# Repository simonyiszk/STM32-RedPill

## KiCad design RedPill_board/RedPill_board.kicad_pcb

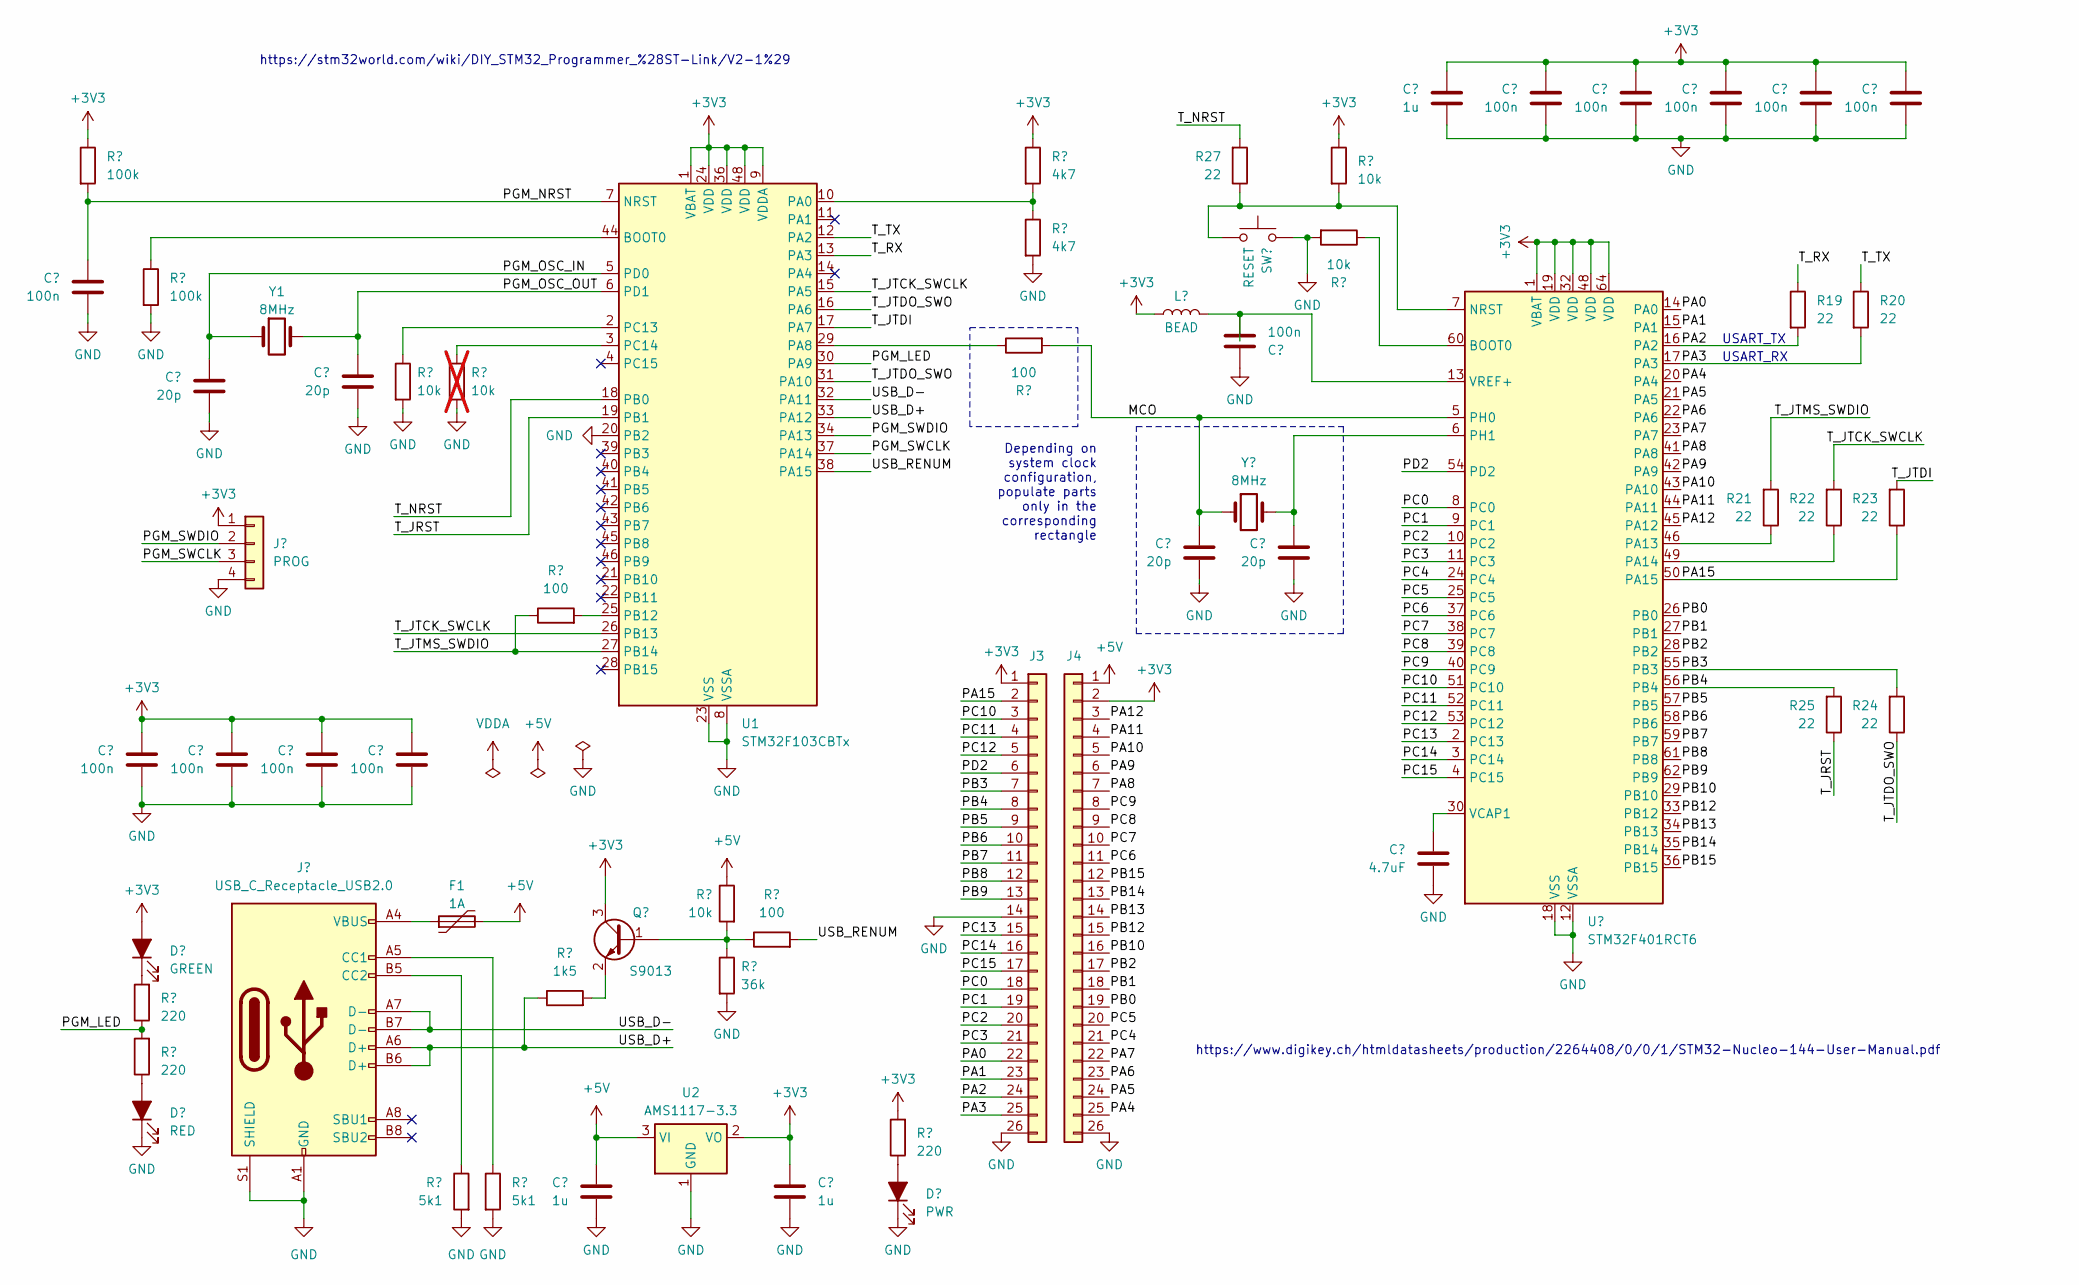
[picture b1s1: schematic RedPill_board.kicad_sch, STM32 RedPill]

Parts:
C1, C2, C3, C5, C7, C12, C15, C16, C17, C18, C19: 100n; C_0603_1608Metric
C4, C6, C10, C11: 20p; C_0603_1608Metric
C8, C9, C14: 1u; C_0603_1608Metric
C13: 4.7uF; C_0805_2012Metric
D1: GREEN; LED_0603_1608Metric
D2: RED; LED_0603_1608Metric
D3: PWR; LED_0603_1608Metric
F1: 1A; Fuse_1206_3216Metric
J1: PROG; PinHeader_1x04_P1.27mm_Vertical
J2: USB_C_Receptacle_USB2.0; USB_C_Receptacle_G-Switch_GT-USB-7010ASV
J3, J4: Conn_01x26; PinHeader_1x26_P2.54mm_Vertical
L1: BEAD; L_0603_1608Metric
Q1: S9013; SOT-23
R1, R4: 100k; R_0603_1608Metric
R2, R3, R15: 220; R_0603_1608Metric
R5, R11, R18, R26: 10k; R_0603_1608Metric
R6: 10k; R_0603_1608Metric; not fitted
R7, R8: 5k1; R_0603_1608Metric
R9, R13, R14: 100; R_0603_1608Metric
R10: 1k5; R_0603_1608Metric
R12: 36k; R_0603_1608Metric
R16, R17: 4k7; R_0603_1608Metric
R19, R20, R21, R22, R23, R24, R25, R27: 22; R_0603_1608Metric
SW1: RESET; SW_SPST_TL3342
U1: STM32F103CBTx; LQFP-48_7x7mm_P0.5mm
U2: AMS1117-3.3; SOT-223-3_TabPin2
U3: STM32F401RCT6; LQFP-64_10x10mm_P0.5mm
Y1: 8MHz; Crystal_SMD_5032-2Pin_5.0x3.2mm
Y2: 8MHz; Crystal_HC49-4H_Vertical

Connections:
+3V3: C2.1, C3.1, C5.1, C7.1, C9.1, C14.1, C15.1, C16.1, C17.1, C18.1, C19.1, D1.2 (A), J1.1, J3.1, J4.2, L1.1, Q1.3 (C), R1.1, R15.2, R16.1, R26.1, U1.1 (VBAT), U1.9 (VDDA), U1.24 (VDD), U1.36 (VDD), U1.48 (VDD), U2.2 (VO), U3.1 (VBAT), U3.19 (VDD), U3.32 (VDD), U3.48 (VDD), U3.64 (VDD)
+5V: C8.1, F1.2, J4.1, R11.1, U2.3 (VI)
/MCO: C10.1, R14.2, U3.5 (PH0), Y2.1
/PA0: J3.22, U3.14 (PA0)
/PA1: J3.23, U3.15 (PA1)
/PA2: J3.24, R19.2, U3.16 (PA2)
/PA3: J3.25, R20.2, U3.17 (PA3)
/PA4: J4.25, U3.20 (PA4)
/PA5: J4.24, U3.21 (PA5)
/PA6: J4.23, U3.22 (PA6)
/PA7: J4.22, U3.23 (PA7)
/PA8: J4.7, U3.41 (PA8)
/PA9: J4.6, U3.42 (PA9)
/PA10: J4.5, U3.43 (PA10)
/PA11: J4.4, U3.44 (PA11)
/PA12: J4.3, U3.45 (PA12)
/PA15: J3.2, R23.1, U3.50 (PA15)
/PB0: J4.19, U3.26 (PB0)
/PB1: J4.18, U3.27 (PB1)
/PB2: J4.17, U3.28 (PB2)
/PB3: J3.7, R24.2, U3.55 (PB3)
/PB4: J3.8, R25.2, U3.56 (PB4)
/PB5: J3.9, U3.57 (PB5)
/PB6: J3.10, U3.58 (PB6)
/PB7: J3.11, U3.59 (PB7)
/PB8: J3.12, U3.61 (PB8)
/PB9: J3.13, U3.62 (PB9)
/PB10: J4.16, U3.29 (PB10)
/PB12: J4.15, U3.33 (PB12)
/PB13: J4.14, U3.34 (PB13)
/PB14: J4.13, U3.35 (PB14)
/PB15: J4.12, U3.36 (PB15)
/PC0: J3.18, U3.8 (PC0)
/PC1: J3.19, U3.9 (PC1)
/PC2: J3.20, U3.10 (PC2)
/PC3: J3.21, U3.11 (PC3)
/PC4: J4.21, U3.24 (PC4)
/PC5: J4.20, U3.25 (PC5)
/PC6: J4.11, U3.37 (PC6)
/PC7: J4.10, U3.38 (PC7)
/PC8: J4.9, U3.39 (PC8)
/PC9: J4.8, U3.40 (PC9)
/PC10: J3.3, U3.51 (PC10)
/PC11: J3.4, U3.52 (PC11)
/PC12: J3.5, U3.53 (PC12)
/PC13: J3.15, U3.2 (PC13)
/PC14: J3.16, U3.3 (PC14)
/PC15: J3.17, U3.4 (PC15)
/PD2: J3.6, U3.54 (PD2)
/PGM_LED: R2.1, R3.2, U1.30 (PA9)
/PGM_NRST: C1.1, R1.2, U1.7 (NRST)
/PGM_OSC_IN: C4.1, U1.5 (PD0), Y1.1
/PGM_OSC_OUT: C6.1, U1.6 (PD1), Y1.2
/PGM_SWCLK: J1.3, U1.37 (PA14)
/PGM_SWDIO: J1.2, U1.34 (PA13)
/T_JRST: R25.1, U1.19 (PB1)
/T_JTCK_SWCLK: R22.2, U1.15 (PA5), U1.26 (PB13)
/T_JTDI: R23.2, U1.17 (PA7)
/T_JTDO_SWO: R24.1, U1.16 (PA6), U1.31 (PA10)
/T_JTMS_SWDIO: R9.1, R21.2, U1.27 (PB14)
/T_NRST: R27.2, U1.18 (PB0)
/T_RX: R19.1, U1.13 (PA3)
/T_TX: R20.1, U1.12 (PA2)
/USB_D+: J2.A6 (D+), J2.B6 (D+), R10.1, U1.33 (PA12)
/USB_D-: J2.A7 (D-), J2.B7 (D-), U1.32 (PA11)
/USB_RENUM: R13.2, U1.38 (PA15)
GND: C1.2, C2.2, C3.2, C4.2, C5.2, C6.2, C7.2, C8.2, C9.2, C10.2, C11.2, C12.1, C13.2, C14.2, C15.2, C16.2, C17.2, C18.2, C19.2, D2.1 (K), D3.1 (K), J1.4, J2.A1 (GND), J2.A12 (GND), J2.B1 (GND), J2.B12 (GND), J2.S1 (SHIELD), J3.14, J3.26, J4.26, R4.2, R5.2, R6.2, R7.2, R8.2, R12.2, R17.2, R18.2, SW1.2, U1.8 (VSSA), U1.20 (PB2), U1.23 (VSS), U1.35 (VSS), U1.47 (VSS), U2.1 (GND), U3.12 (VSSA), U3.18 (VSS), U3.31 (VSS), U3.47 (VSS), U3.63 (VSS)
unnamed: D1.1 (K), R2.2
unnamed: D2.2 (A), R3.1
unnamed: D3.2 (A), R15.1
unnamed: F1.1, J2.A4 (VBUS), J2.A9 (VBUS), J2.B4 (VBUS), J2.B9 (VBUS)
unnamed: J2.A5 (CC1), R8.1
unnamed: J2.B5 (CC2), R7.1
unnamed: Q1.1 (B), R11.2, R12.1, R13.1
unnamed: Q1.2 (E), R10.2
unnamed: R4.1, U1.44 (BOOT0)
unnamed: R16.2, R17.1, U1.10 (PA0)
unnamed: R14.1, U1.29 (PA8)
unnamed: R9.2, U1.25 (PB12)
unnamed: R5.1, U1.2 (PC13)
unnamed: R6.1, U1.3 (PC14)
unnamed: R18.1, U3.60 (BOOT0)
unnamed: R26.2, R27.1, SW1.1, U3.7 (NRST)
unnamed: R21.1, U3.46 (PA13)
unnamed: R22.1, U3.49 (PA14)
unnamed: C11.1, U3.6 (PH1), Y2.2
unnamed: C13.1, U3.30 (VCAP1)
unnamed: C12.2, L1.2, U3.13 (VREF+)

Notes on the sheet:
Depending on system clock configuration, populate parts only in the corresponding rectangle
https://stm32world.com/wiki/DIY_STM32_Programmer_%28ST-Link/V2-1%29
USART_RX
USART_TX
https://www.digikey.ch/htmldatasheets/production/2264408/0/0/1/STM32-Nucleo-144-User-Manual.pdf

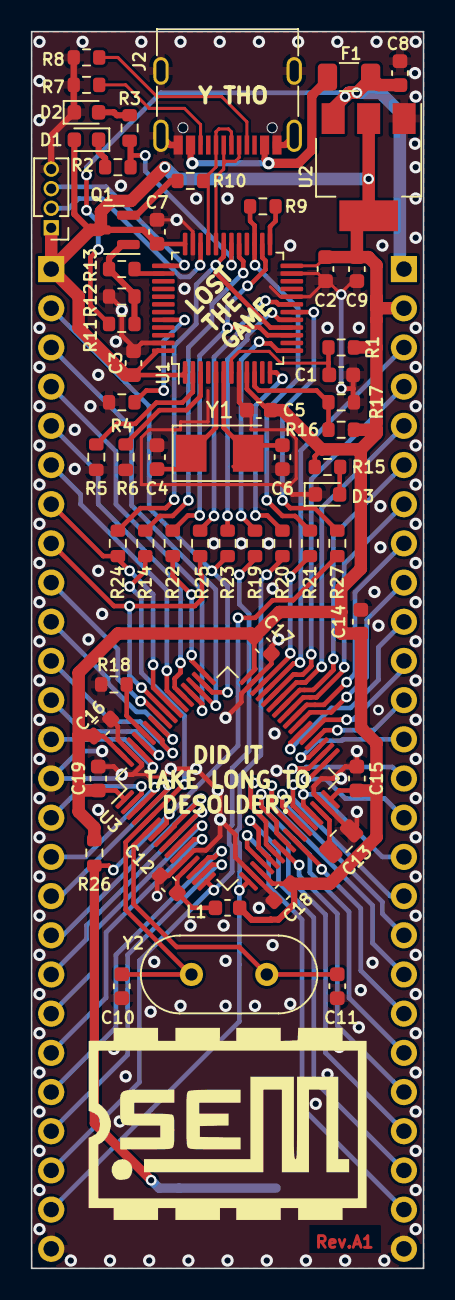
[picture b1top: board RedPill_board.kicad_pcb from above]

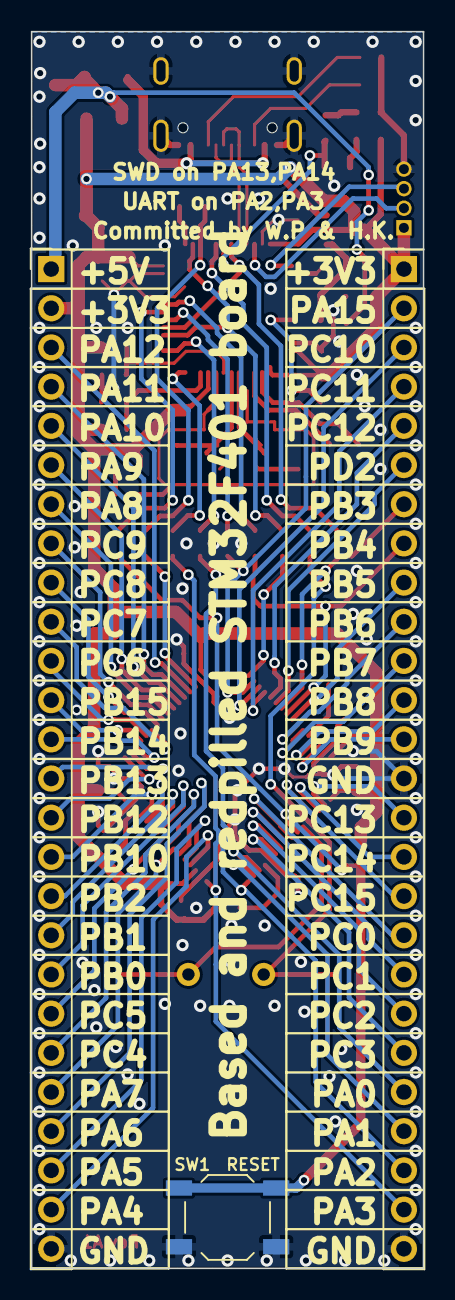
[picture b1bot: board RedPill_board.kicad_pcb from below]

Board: 2 copper layers, 25.4 x 80.2 mm, 62 parts (3 on the bottom side), 88 nets.

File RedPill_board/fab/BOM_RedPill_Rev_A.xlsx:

Comment | Designator | Footprint | JLCPCB Part #（optional）
RESET | SW1 | SW_SPST_TL3342 | C318884
100n | C5,C17,C12,C18,C7,C15,C2,C1,C16,C19,C3 | C_0603_1608Metric | C14663
4.7uF | C13 | C_0805_2012Metric | C1779
4k7 | R16,R17 | R_0603_1608Metric | C23162
36k | R12 | R_0603_1608Metric | C23147
20p | C6,C10,C4,C11 | C_0603_1608Metric | C1648
AMS1117-3.3 | U2 | SOT-223-3_TabPin2 | C6186
220 | R3,R15,R2 | R_0603_1608Metric | C22962
22 | R19,R23,R22,R27,R25,R24,R20,R21 | R_0603_1608Metric | C23345
5k1 | R7,R8 | R_0603_1608Metric | C23186
10k | R6,R18,R26,R11,R5 | R_0603_1608Metric | C25804
1k5 | R10 | R_0603_1608Metric | C22843
RED | D2 | LED_0603_1608Metric | C2286
100 | R13,R14,R9 | R_0603_1608Metric | C22775
GREEN | D1 | LED_0603_1608Metric | C72043
1u | C9,C8,C14 | C_0603_1608Metric | C15849
100k | R1,R4 | R_0603_1608Metric | C25803
PWR | D3 | LED_0603_1608Metric | C2286
FCM32F103CBT6 | U1 | LQFP-48_7x7mm_P0.5mm | C2972837
S9013 | Q1 | SOT-23 | C6749
STM32F401RCT6 | U3 | LQFP-64_10x10mm_P0.5mm | C74524
USB_C_Receptacle_USB2.0 | J2 | USB_C_Receptacle_G-Switch_GT-USB-7010ASV | C2765186
8MHz | Y1 | Crystal_SMD_5032_2pin | C115962
BEAD | L1 | L_0603_1608Metric | C1002
1A | F1 | Fuse_1206_3216Metric | C883131

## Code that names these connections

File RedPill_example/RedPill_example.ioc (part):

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Mcu.Name=STM32F401R(B-C)Tx
Mcu.Package=LQFP64
Mcu.UserName=STM32F401RCTx
PA13.Mode=Serial_Wire
PA13.Signal=SYS_JTMS-SWDIO
PA14.Mode=Serial_Wire
PA14.Signal=SYS_JTCK-SWCLK
PA2.Mode=Asynchronous
PA2.Signal=USART2_TX
PA3.Mode=Asynchronous
PA3.Signal=USART2_RX
PH0\ -\ OSC_IN.Mode=HSE-External-Clock-Source
PH0\ -\ OSC_IN.Signal=RCC_OSC_IN
PH1\ -\ OSC_OUT.Mode=HSE-External-Clock-Source
PH1\ -\ OSC_OUT.Signal=RCC_OSC_OUT
RCC.HSE_VALUE=8000000
RCC.SYSCLKFreq_VALUE=84000000
RCC.SYSCLKSource=RCC_SYSCLKSOURCE_PLLCLK
board=custom

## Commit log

2023-06-29 Add kicad project containing main board with initial schematic
2023-06-30 Cleanup programming nets and components, add blank connectors and initial pcb design
2023-07-22 Minor modifications
2023-07-23 Fit parts on top side
2023-08-06 Routing in progress.
2023-08-07 Routed.
2023-08-07 Added texts and logo.
2023-08-08 Reviewed.
2023-08-08 Sent to fab.
2023-08-24 Revision A1 + UART test firmware.
2023-09-09 Add licence.
2025-07-22 add schematic pdf
